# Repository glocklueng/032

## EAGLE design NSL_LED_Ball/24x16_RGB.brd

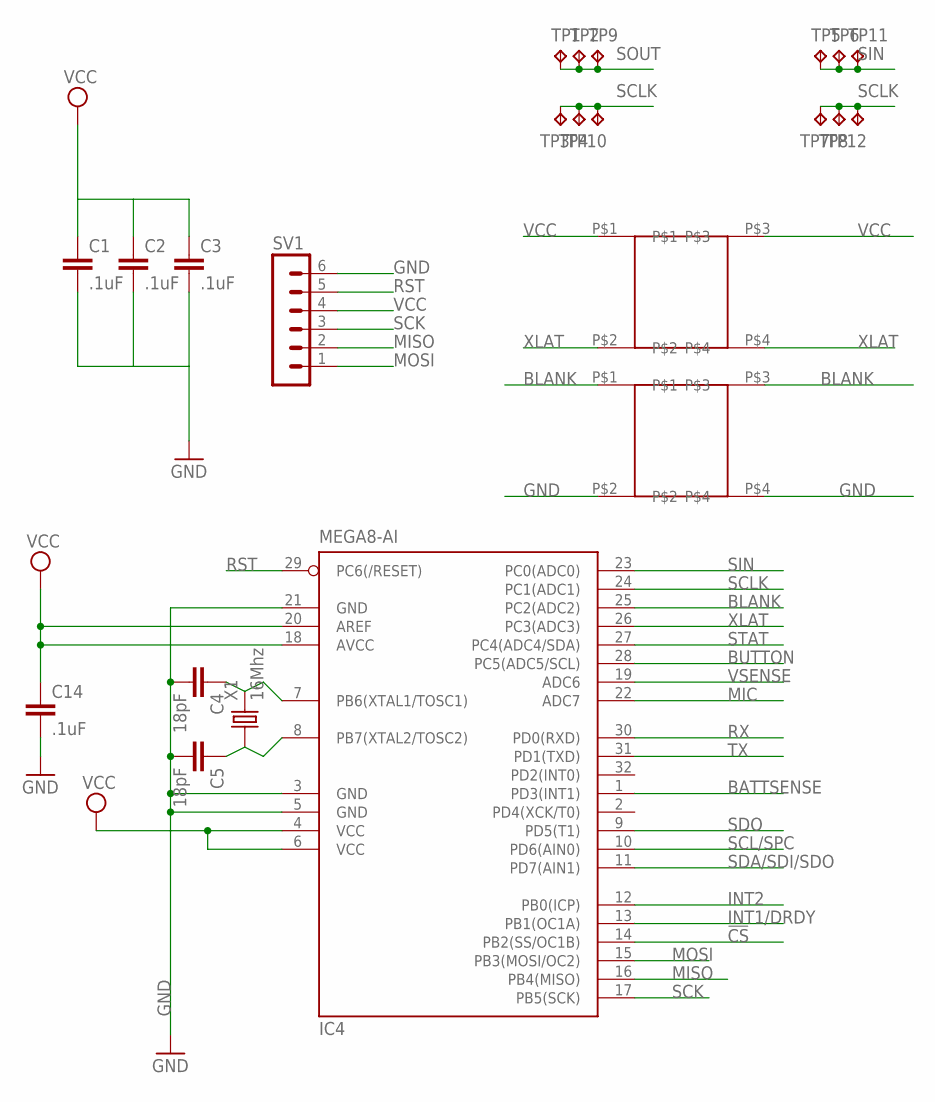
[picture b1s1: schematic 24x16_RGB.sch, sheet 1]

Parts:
C1, C2, C3, C14: .1uF; 0805
C4, C5: 18pF; 0805
IC4: MEGA8-AI; TQFP32-08
SLOT1, SLOT2: SLOT
SV1: MA06-1
TP1, TP2, TP3, TP4, TP5, TP6, TP7, TP8, TP9, TP10, TP11, TP12: TPTP20SQ; TP20SQ
X1: 16Mhz; 5032

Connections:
!CS: IC4.14 (PB2(SS/OC1B)); also elsewhere on the board
BATTSENSE: IC4.1 (PD3(INT1))
BLANK: IC4.25 (PC2(ADC2)), SLOT2.P$1, SLOT2.P$3; also elsewhere on the board
BUTTON: IC4.28 (PC5(ADC5/SCL)); also elsewhere on the board
GND: C1.2, C2.2, C3.2, C4.2, C5.2, C14.2, IC4.3 (GND), IC4.5 (GND), IC4.21 (GND), SLOT2.P$2, SLOT2.P$4, SV1.6; also elsewhere on the board
INT1/DRDY: IC4.13 (PB1(OC1A)); also elsewhere on the board
INT2: IC4.12 (PB0(ICP)); also elsewhere on the board
MIC: IC4.22 (ADC7); also elsewhere on the board
MISO: IC4.16 (PB4(MISO)), SV1.2
MOSI: IC4.15 (PB3(MOSI/OC2)), SV1.1
unnamed: C4.1, IC4.7 (PB6(XTAL1/TOSC1)), X1.2
unnamed: C5.1, IC4.8 (PB7(XTAL2/TOSC2)), X1.1
RST: IC4.29 (PC6(/RESET)), SV1.5; also elsewhere on the board
RX: IC4.30 (PD0(RXD)); also elsewhere on the board
SCK: IC4.17 (PB5(SCK)), SV1.3
SCL/SPC: IC4.10 (PD6(AIN0)); also elsewhere on the board
SCLK: IC4.24 (PC1(ADC1)), TP3.TP, TP4.TP, TP7.TP, TP8.TP, TP10.TP, TP12.TP; also elsewhere on the board
SDA/SDI/SDO: IC4.11 (PD7(AIN1)); also elsewhere on the board
SDO: IC4.9 (PD5(T1)); also elsewhere on the board
SIN: IC4.23 (PC0(ADC0)), TP5.TP, TP6.TP, TP11.TP; also elsewhere on the board
SOUT: TP1.TP, TP2.TP, TP9.TP; also elsewhere on the board
STAT: IC4.27 (PC4(ADC4/SDA)); also elsewhere on the board
TX: IC4.31 (PD1(TXD)); also elsewhere on the board
VCC: C1.1, C2.1, C3.1, C14.1, IC4.4 (VCC), IC4.6 (VCC), IC4.18 (AVCC), IC4.20 (AREF), SLOT1.P$1, SLOT1.P$3, SV1.4; also elsewhere on the board
VSENSE: IC4.19 (ADC6)
XLAT: IC4.26 (PC3(ADC3)), SLOT1.P$2, SLOT1.P$4; also elsewhere on the board

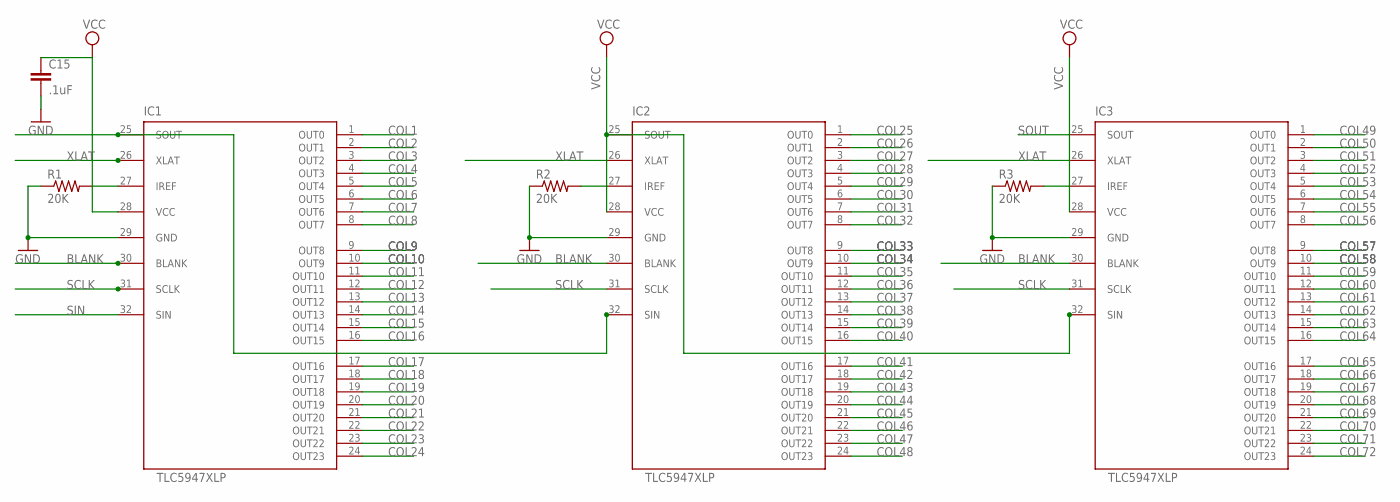
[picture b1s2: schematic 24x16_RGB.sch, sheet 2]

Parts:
C15: .1uF; 0805
IC1, IC2, IC3: TLC5947XLP; QFN32_XLP
R1, R2, R3: 20K; R0805

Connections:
BLANK: IC1.30 (BLANK), IC2.30 (BLANK), IC3.30 (BLANK); also elsewhere on the board
COL1: IC1.1 (OUT0); also elsewhere on the board
COL2: IC1.2 (OUT1); also elsewhere on the board
COL3: IC1.3 (OUT2); also elsewhere on the board
COL4: IC1.4 (OUT3); also elsewhere on the board
COL5: IC1.5 (OUT4); also elsewhere on the board
COL6: IC1.6 (OUT5); also elsewhere on the board
COL7: IC1.7 (OUT6); also elsewhere on the board
COL8: IC1.8 (OUT7); also elsewhere on the board
COL9: IC1.9 (OUT8); also elsewhere on the board
COL10: IC1.10 (OUT9); also elsewhere on the board
COL11: IC1.11 (OUT10); also elsewhere on the board
COL12: IC1.12 (OUT11); also elsewhere on the board
COL13: IC1.13 (OUT12); also elsewhere on the board
COL14: IC1.14 (OUT13); also elsewhere on the board
COL15: IC1.15 (OUT14); also elsewhere on the board
COL16: IC1.16 (OUT15); also elsewhere on the board
COL17: IC1.17 (OUT16); also elsewhere on the board
COL18: IC1.18 (OUT17); also elsewhere on the board
COL19: IC1.19 (OUT18); also elsewhere on the board
COL20: IC1.20 (OUT19); also elsewhere on the board
COL21: IC1.21 (OUT20); also elsewhere on the board
COL22: IC1.22 (OUT21); also elsewhere on the board
COL23: IC1.23 (OUT22); also elsewhere on the board
COL24: IC1.24 (OUT23); also elsewhere on the board
COL25: IC2.1 (OUT0); also elsewhere on the board
COL26: IC2.2 (OUT1); also elsewhere on the board
COL27: IC2.3 (OUT2); also elsewhere on the board
COL28: IC2.4 (OUT3); also elsewhere on the board
COL29: IC2.5 (OUT4); also elsewhere on the board
COL30: IC2.6 (OUT5); also elsewhere on the board
COL31: IC2.7 (OUT6); also elsewhere on the board
COL32: IC2.8 (OUT7); also elsewhere on the board
COL33: IC2.9 (OUT8); also elsewhere on the board
COL34: IC2.10 (OUT9); also elsewhere on the board
COL35: IC2.11 (OUT10); also elsewhere on the board
COL36: IC2.12 (OUT11); also elsewhere on the board
COL37: IC2.13 (OUT12); also elsewhere on the board
COL38: IC2.14 (OUT13); also elsewhere on the board
COL39: IC2.15 (OUT14); also elsewhere on the board
COL40: IC2.16 (OUT15); also elsewhere on the board
COL41: IC2.17 (OUT16); also elsewhere on the board
COL42: IC2.18 (OUT17); also elsewhere on the board
COL43: IC2.19 (OUT18); also elsewhere on the board
COL44: IC2.20 (OUT19); also elsewhere on the board
COL45: IC2.21 (OUT20); also elsewhere on the board
COL46: IC2.22 (OUT21); also elsewhere on the board
COL47: IC2.23 (OUT22); also elsewhere on the board
COL48: IC2.24 (OUT23); also elsewhere on the board
COL49: IC3.1 (OUT0); also elsewhere on the board
COL50: IC3.2 (OUT1); also elsewhere on the board
COL51: IC3.3 (OUT2); also elsewhere on the board
COL52: IC3.4 (OUT3); also elsewhere on the board
COL53: IC3.5 (OUT4); also elsewhere on the board
COL54: IC3.6 (OUT5); also elsewhere on the board
COL55: IC3.7 (OUT6); also elsewhere on the board
COL56: IC3.8 (OUT7); also elsewhere on the board
COL57: IC3.9 (OUT8); also elsewhere on the board
COL58: IC3.10 (OUT9); also elsewhere on the board
COL59: IC3.11 (OUT10); also elsewhere on the board
COL60: IC3.12 (OUT11); also elsewhere on the board
COL61: IC3.13 (OUT12); also elsewhere on the board
COL62: IC3.14 (OUT13); also elsewhere on the board
COL63: IC3.15 (OUT14); also elsewhere on the board
COL64: IC3.16 (OUT15); also elsewhere on the board
COL65: IC3.17 (OUT16); also elsewhere on the board
COL66: IC3.18 (OUT17); also elsewhere on the board
COL67: IC3.19 (OUT18); also elsewhere on the board
COL68: IC3.20 (OUT19); also elsewhere on the board
COL69: IC3.21 (OUT20); also elsewhere on the board
COL70: IC3.22 (OUT21); also elsewhere on the board
COL71: IC3.23 (OUT22); also elsewhere on the board
COL72: IC3.24 (OUT23); also elsewhere on the board
GND: C15.2, IC1.29 (GND), IC2.29 (GND), IC3.29 (GND), R1.1, R2.1, R3.1; also elsewhere on the board
HOLE: IC1.27 (IREF), R1.2
unnamed: IC2.27 (IREF), R2.2
unnamed: IC1.25 (SOUT), IC2.32 (SIN)
unnamed: IC3.27 (IREF), R3.2
unnamed: IC2.25 (SOUT), IC3.32 (SIN)
SCLK: IC1.31 (SCLK), IC2.31 (SCLK), IC3.31 (SCLK); also elsewhere on the board
SIN: IC1.32 (SIN); also elsewhere on the board
SOUT: IC3.25 (SOUT); also elsewhere on the board
VCC: C15.1, IC1.28 (VCC), IC2.28 (VCC), IC3.28 (VCC); also elsewhere on the board
XLAT: IC1.26 (XLAT), IC2.26 (XLAT), IC3.26 (XLAT); also elsewhere on the board

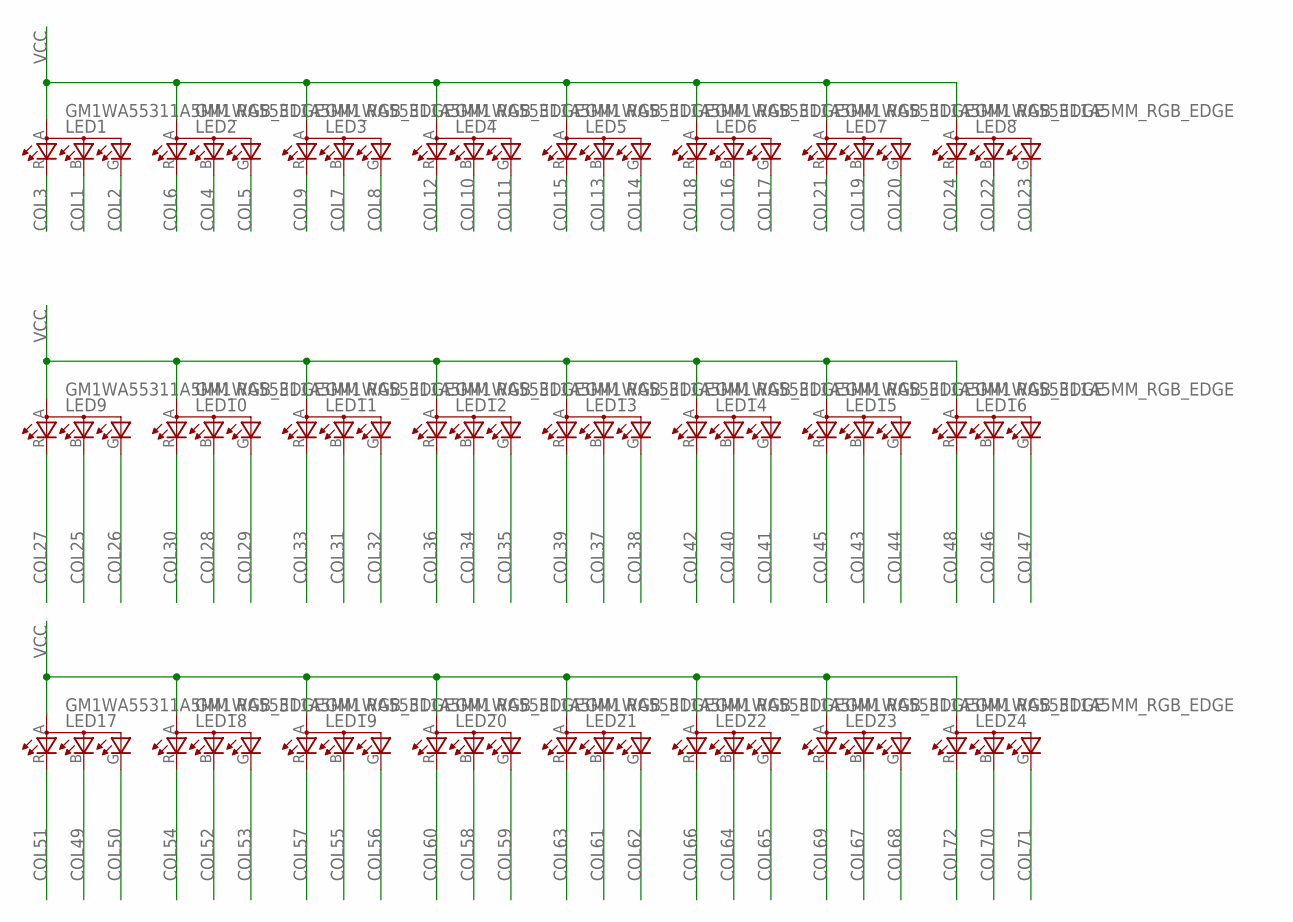
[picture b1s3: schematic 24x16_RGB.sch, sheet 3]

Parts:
LED1, LED2, LED3, LED4, LED5, LED6, LED7, LED8, LED9, LED10, LED11, LED12, LED13, LED14, LED15, LED16, LED17, LED18, LED19, LED20, LED21, LED22, LED23, LED24: GM1WA55311A5MM_RGB_EDGE; LED5MM_RGB_EDGE

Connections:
COL1: LED1.B (CBLUE); also elsewhere on the board
COL2: LED1.G (CGREEN); also elsewhere on the board
COL3: LED1.R (CRED); also elsewhere on the board
COL4: LED2.B (CBLUE); also elsewhere on the board
COL5: LED2.G (CGREEN); also elsewhere on the board
COL6: LED2.R (CRED); also elsewhere on the board
COL7: LED3.B (CBLUE); also elsewhere on the board
COL8: LED3.G (CGREEN); also elsewhere on the board
COL9: LED3.R (CRED); also elsewhere on the board
COL10: LED4.B (CBLUE); also elsewhere on the board
COL11: LED4.G (CGREEN); also elsewhere on the board
COL12: LED4.R (CRED); also elsewhere on the board
COL13: LED5.B (CBLUE); also elsewhere on the board
COL14: LED5.G (CGREEN); also elsewhere on the board
COL15: LED5.R (CRED); also elsewhere on the board
COL16: LED6.B (CBLUE); also elsewhere on the board
COL17: LED6.G (CGREEN); also elsewhere on the board
COL18: LED6.R (CRED); also elsewhere on the board
COL19: LED7.B (CBLUE); also elsewhere on the board
COL20: LED7.G (CGREEN); also elsewhere on the board
COL21: LED7.R (CRED); also elsewhere on the board
COL22: LED8.B (CBLUE); also elsewhere on the board
COL23: LED8.G (CGREEN); also elsewhere on the board
COL24: LED8.R (CRED); also elsewhere on the board
COL25: LED9.B (CBLUE); also elsewhere on the board
COL26: LED9.G (CGREEN); also elsewhere on the board
COL27: LED9.R (CRED); also elsewhere on the board
COL28: LED10.B (CBLUE); also elsewhere on the board
COL29: LED10.G (CGREEN); also elsewhere on the board
COL30: LED10.R (CRED); also elsewhere on the board
COL31: LED11.B (CBLUE); also elsewhere on the board
COL32: LED11.G (CGREEN); also elsewhere on the board
COL33: LED11.R (CRED); also elsewhere on the board
COL34: LED12.B (CBLUE); also elsewhere on the board
COL35: LED12.G (CGREEN); also elsewhere on the board
COL36: LED12.R (CRED); also elsewhere on the board
COL37: LED13.B (CBLUE); also elsewhere on the board
COL38: LED13.G (CGREEN); also elsewhere on the board
COL39: LED13.R (CRED); also elsewhere on the board
COL40: LED14.B (CBLUE); also elsewhere on the board
COL41: LED14.G (CGREEN); also elsewhere on the board
COL42: LED14.R (CRED); also elsewhere on the board
COL43: LED15.B (CBLUE); also elsewhere on the board
COL44: LED15.G (CGREEN); also elsewhere on the board
COL45: LED15.R (CRED); also elsewhere on the board
COL46: LED16.B (CBLUE); also elsewhere on the board
COL47: LED16.G (CGREEN); also elsewhere on the board
COL48: LED16.R (CRED); also elsewhere on the board
COL49: LED17.B (CBLUE); also elsewhere on the board
COL50: LED17.G (CGREEN); also elsewhere on the board
COL51: LED17.R (CRED); also elsewhere on the board
COL52: LED18.B (CBLUE); also elsewhere on the board
COL53: LED18.G (CGREEN); also elsewhere on the board
COL54: LED18.R (CRED); also elsewhere on the board
COL55: LED19.B (CBLUE); also elsewhere on the board
COL56: LED19.G (CGREEN); also elsewhere on the board
COL57: LED19.R (CRED); also elsewhere on the board
COL58: LED20.B (CBLUE); also elsewhere on the board
COL59: LED20.G (CGREEN); also elsewhere on the board
COL60: LED20.R (CRED); also elsewhere on the board
COL61: LED21.B (CBLUE); also elsewhere on the board
COL62: LED21.G (CGREEN); also elsewhere on the board
COL63: LED21.R (CRED); also elsewhere on the board
COL64: LED22.B (CBLUE); also elsewhere on the board
COL65: LED22.G (CGREEN); also elsewhere on the board
COL66: LED22.R (CRED); also elsewhere on the board
COL67: LED23.B (CBLUE); also elsewhere on the board
COL68: LED23.G (CGREEN); also elsewhere on the board
COL69: LED23.R (CRED); also elsewhere on the board
COL70: LED24.B (CBLUE); also elsewhere on the board
COL71: LED24.G (CGREEN); also elsewhere on the board
COL72: LED24.R (CRED); also elsewhere on the board
VCC: LED1.A, LED2.A, LED3.A, LED4.A, LED5.A, LED6.A, LED7.A, LED8.A, LED9.A, LED10.A, LED11.A, LED12.A, LED13.A, LED14.A, LED15.A, LED16.A, LED17.A, LED18.A, LED19.A, LED20.A, LED21.A, LED22.A, LED23.A, LED24.A; also elsewhere on the board

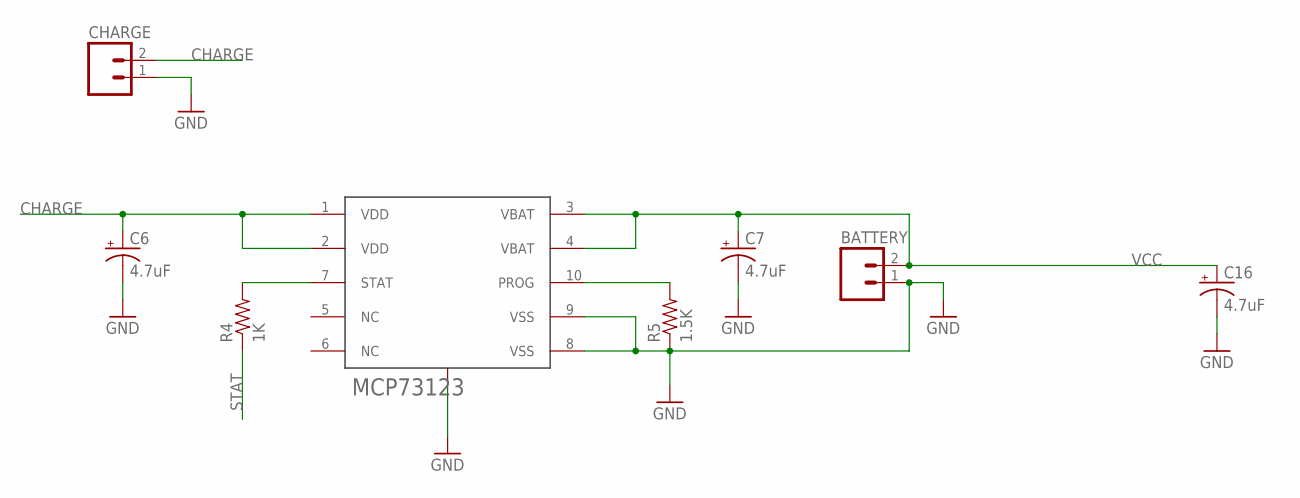
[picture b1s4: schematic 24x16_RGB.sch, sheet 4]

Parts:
BATTERY: M02PTH; 1X02
C6, C7, C16: 4.7uF; EIA3528
CHARGE: M02PTH; 1X02
IC5: MCP73123; DFN10_3X3
R4: 1K; 0805
R5: 1.5K; 0805

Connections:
CHARGE: C6.A (+), CHARGE.2, IC5.1 (VDD), IC5.2 (VDD)
GND: BATTERY.1, C6.C (-), C7.C (-), C16.C (-), CHARGE.1, IC5.8 (VSS), IC5.9 (VSS), IC5.EXP (GND), R5.1; also elsewhere on the board
unnamed: IC5.7 (STAT), R4.2
unnamed: IC5.10 (PROG), R5.2
STAT: R4.1; also elsewhere on the board
VCC: BATTERY.2, C7.A (+), C16.A (+), IC5.3 (VBAT), IC5.4 (VBAT); also elsewhere on the board

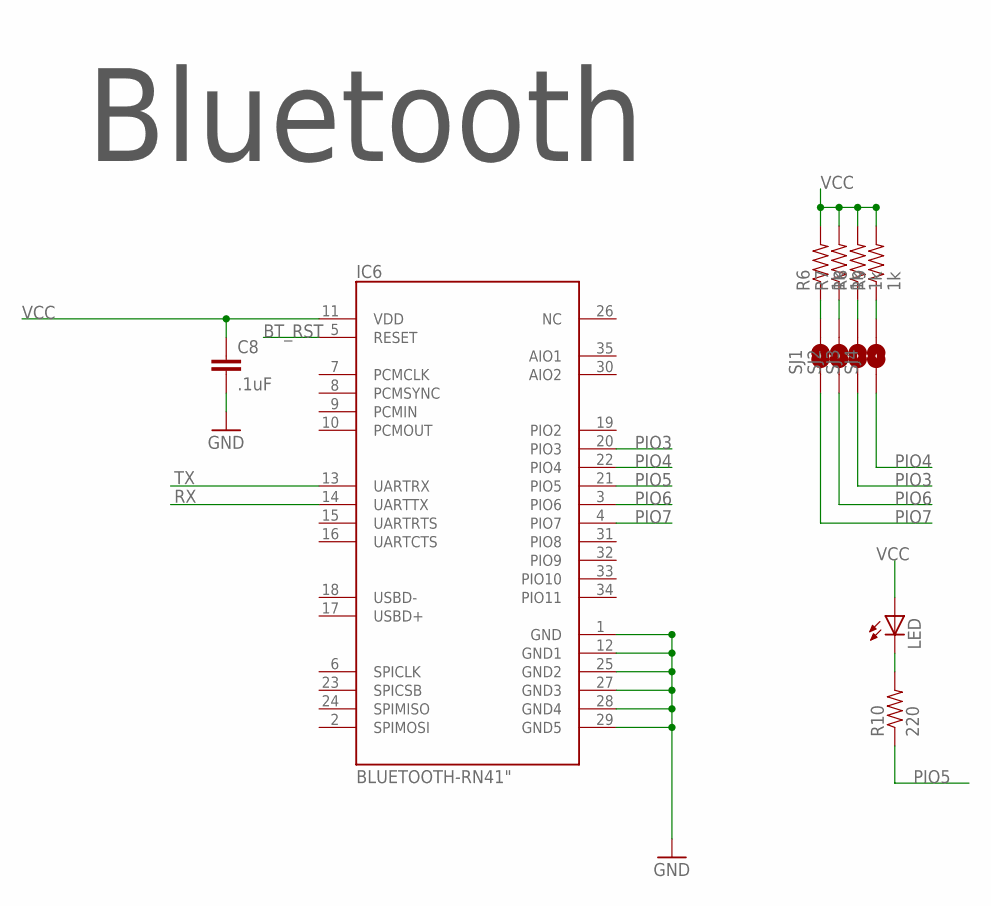
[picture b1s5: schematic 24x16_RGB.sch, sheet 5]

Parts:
C8: .1uF; 0805
IC6: BLUETOOTH-RN41"; RN41
LED: LEDCHIP-LED0603; CHIP-LED0603
R6, R7, R8, R9: 1k; 0805
R10: 220; 0805
SJ1, SJ2, SJ3, SJ4: SOLDERJUMPERNO; SJ_2S-NO

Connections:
BT_RST: IC6.5 (RESET); also elsewhere on the board
GND: C8.2, IC6.1 (GND), IC6.12 (GND1), IC6.25 (GND2), IC6.27 (GND3), IC6.28 (GND4), IC6.29 (GND5); also elsewhere on the board
unnamed: LED.C, R10.2
unnamed: R6.1, SJ1.2
unnamed: R8.1, SJ3.2
unnamed: R7.1, SJ2.2
unnamed: R9.1, SJ4.2
PIO3: IC6.20 (PIO3), SJ3.1
PIO4: IC6.22 (PIO4), SJ4.1
PIO5: IC6.21 (PIO5), R10.1
PIO6: IC6.3 (PIO6), SJ2.1
PIO7: IC6.4 (PIO7), SJ1.1
RX: IC6.14 (UARTTX); also elsewhere on the board
TX: IC6.13 (UARTRX); also elsewhere on the board
VCC: C8.1, IC6.11 (VDD), LED.A, R6.2, R7.2, R8.2, R9.2; also elsewhere on the board

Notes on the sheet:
Bluetooth

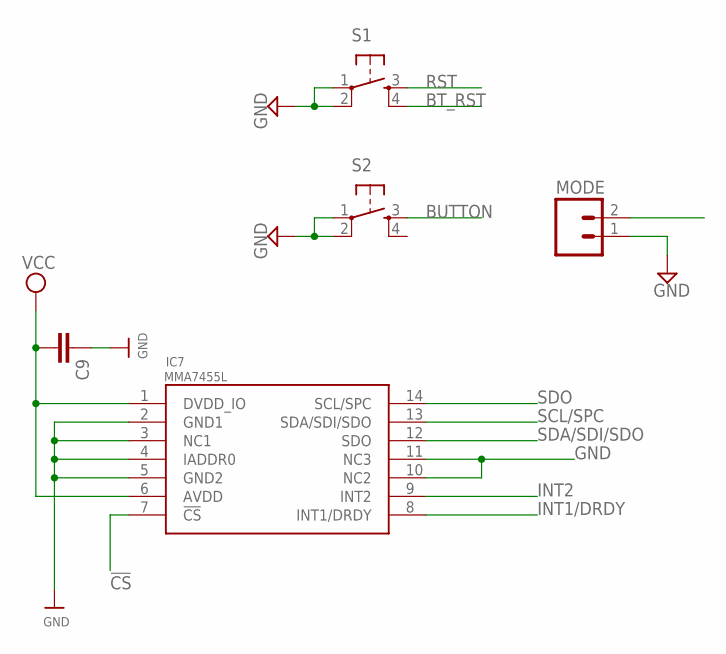
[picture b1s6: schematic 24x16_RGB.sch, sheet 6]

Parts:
C9: CAP0805; 0805
IC7: MMA7455L; LGA-14
MODE: M02PTH; 1X02
S1, S2: TAC_SWITCHSMD; TACTILE_SWITCH_SMD

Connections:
!CS: IC7.7 (!CS); also elsewhere on the board
BT_RST: S1.4; also elsewhere on the board
BUTTON: MODE.2, S2.3; also elsewhere on the board
GND: C9.1, IC7.2 (GND1), IC7.3 (NC1), IC7.4 (IADDR0), IC7.5 (GND2), IC7.10 (NC2), IC7.11 (NC3), MODE.1, S1.1, S1.2, S2.1, S2.2; also elsewhere on the board
INT1/DRDY: IC7.8 (INT1/DRDY); also elsewhere on the board
INT2: IC7.9 (INT2); also elsewhere on the board
RST: S1.3; also elsewhere on the board
SCL/SPC: IC7.13 (SDA/SDI/SDO); also elsewhere on the board
SDA/SDI/SDO: IC7.12 (SDO); also elsewhere on the board
SDO: IC7.14 (SCL/SPC); also elsewhere on the board
VCC: C9.2, IC7.1 (DVDD_IO), IC7.6 (AVDD); also elsewhere on the board

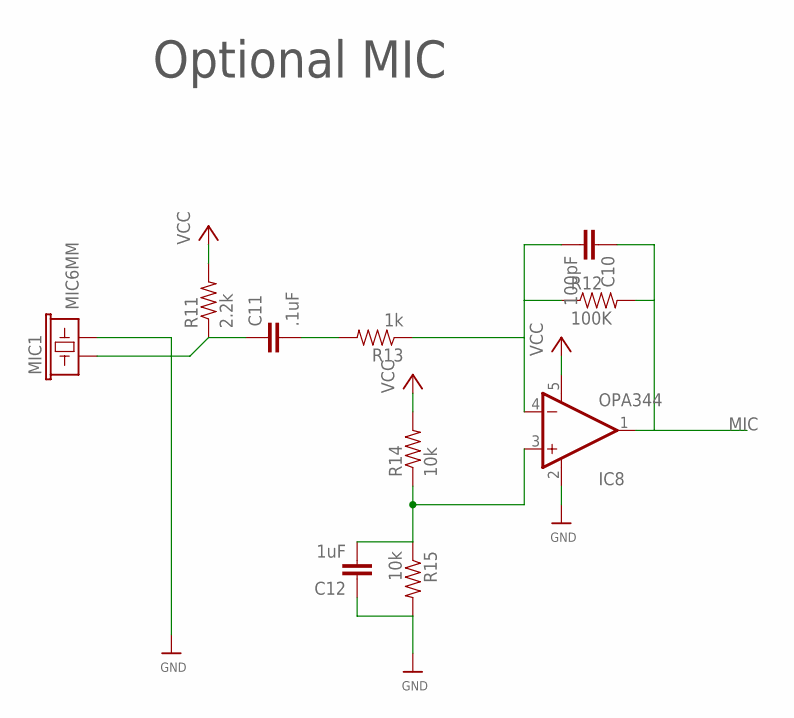
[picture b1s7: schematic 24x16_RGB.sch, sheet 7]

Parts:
C10: 100pF; 0805
C11: .1uF; 0805
C12: 1uF; 0805
IC8: OPA344; SOT23-5
MIC1: MIC6MM; MIC-6MM
R11: 2.2k; 0805
R12: 100K; 0805
R13: 1k; 0805
R14, R15: 10k; 0805

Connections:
GND: C12.1, IC8.2 (V-), MIC1.2, R15.2; also elsewhere on the board
MIC: C10.1, IC8.1 (OUT), R12.2; also elsewhere on the board
unnamed: C11.2, R13.2
unnamed: C11.1, MIC1.1, R11.1
unnamed: C12.2, IC8.3 (+IN), R14.1, R15.1
unnamed: C10.2, IC8.4 (-IN), R12.1, R13.1
VCC: IC8.5 (V+), R11.2, R14.2; also elsewhere on the board

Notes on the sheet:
Optional MIC

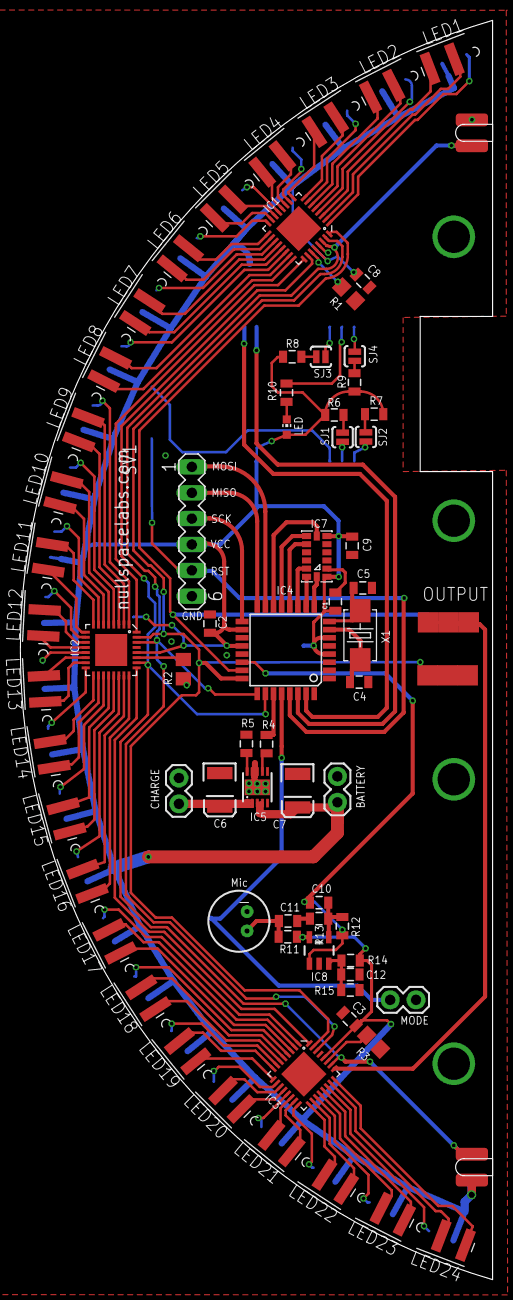
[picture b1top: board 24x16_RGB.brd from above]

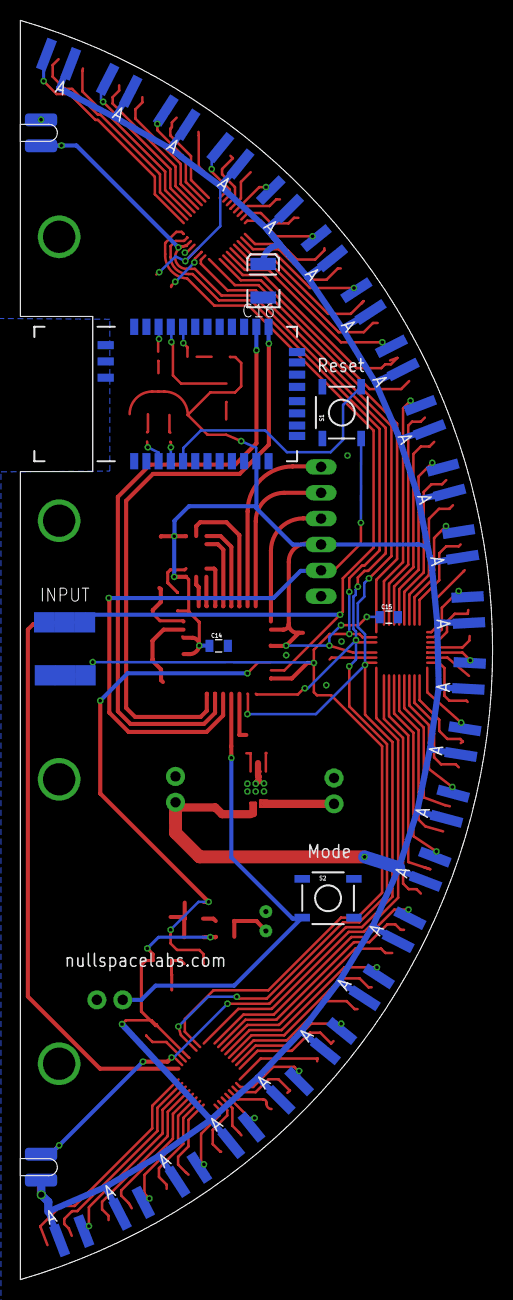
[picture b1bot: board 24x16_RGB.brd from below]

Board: 2 copper layers, 46.4 x 123.7 mm, 89 parts (12 on the bottom side), 119 nets.

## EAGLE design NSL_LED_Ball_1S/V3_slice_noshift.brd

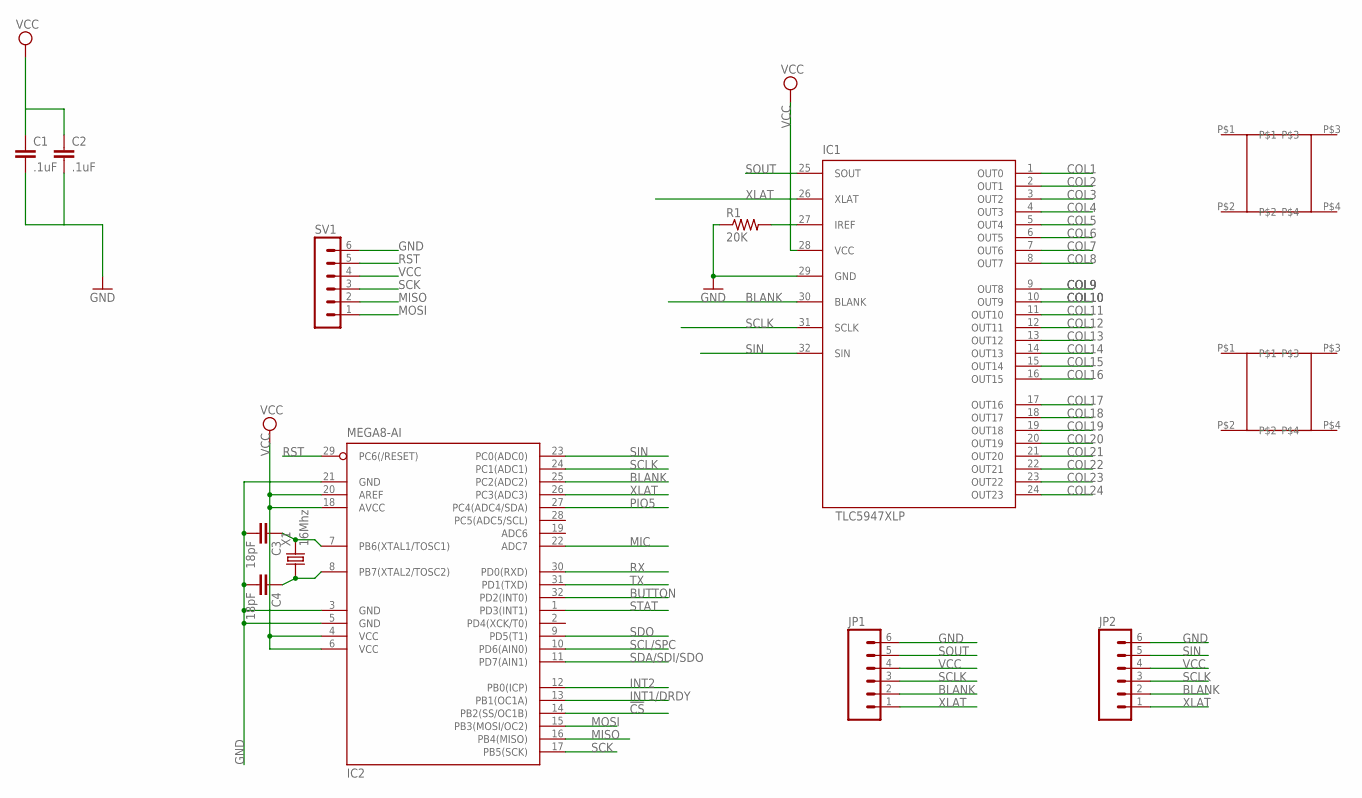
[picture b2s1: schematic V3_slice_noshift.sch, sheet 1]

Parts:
C1, C2: .1uF; 0805
C3, C4: 18pF; 0805
IC1: TLC5947XLP; QFN32_XLP
IC2: MEGA8-AI; TQFP32-08
JP1, JP2: M061X06-SMD_EDGE_FEMALE; 1X06-SMD_EDGE
R1: 20K; R0805
SLOT1, SLOT2: SLOT
SV1: MA06-1
X1: 16Mhz; 5032

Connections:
!CS: IC2.14 (PB2(SS/OC1B)); also elsewhere on the board
BLANK: IC1.30 (BLANK), IC2.25 (PC2(ADC2)), JP1.2, JP2.2
BUTTON: IC2.32 (PD2(INT0)); also elsewhere on the board
COL1: IC1.1 (OUT0); also elsewhere on the board
COL2: IC1.2 (OUT1); also elsewhere on the board
COL3: IC1.3 (OUT2); also elsewhere on the board
COL4: IC1.4 (OUT3); also elsewhere on the board
COL5: IC1.5 (OUT4); also elsewhere on the board
COL6: IC1.6 (OUT5); also elsewhere on the board
COL7: IC1.7 (OUT6); also elsewhere on the board
COL8: IC1.8 (OUT7); also elsewhere on the board
COL9: IC1.9 (OUT8); also elsewhere on the board
COL10: IC1.10 (OUT9); also elsewhere on the board
COL11: IC1.11 (OUT10); also elsewhere on the board
COL12: IC1.12 (OUT11); also elsewhere on the board
COL13: IC1.13 (OUT12); also elsewhere on the board
COL14: IC1.14 (OUT13); also elsewhere on the board
COL15: IC1.15 (OUT14); also elsewhere on the board
COL16: IC1.16 (OUT15); also elsewhere on the board
COL17: IC1.17 (OUT16); also elsewhere on the board
COL18: IC1.18 (OUT17); also elsewhere on the board
COL19: IC1.19 (OUT18); also elsewhere on the board
COL20: IC1.20 (OUT19); also elsewhere on the board
COL21: IC1.21 (OUT20); also elsewhere on the board
COL22: IC1.22 (OUT21); also elsewhere on the board
COL23: IC1.23 (OUT22); also elsewhere on the board
COL24: IC1.24 (OUT23); also elsewhere on the board
GND: C1.2, C2.2, C3.2, C4.2, IC1.29 (GND), IC2.3 (GND), IC2.5 (GND), IC2.21 (GND), JP1.6, JP2.6, R1.1, SV1.6; also elsewhere on the board
INT1/DRDY: IC2.13 (PB1(OC1A)); also elsewhere on the board
INT2: IC2.12 (PB0(ICP)); also elsewhere on the board
MIC: IC2.22 (ADC7); also elsewhere on the board
MISO: IC2.16 (PB4(MISO)), SV1.2
MOSI: IC2.15 (PB3(MOSI/OC2)), SV1.1
unnamed: C3.1, IC2.7 (PB6(XTAL1/TOSC1)), X1.2
unnamed: C4.1, IC2.8 (PB7(XTAL2/TOSC2)), X1.1
unnamed: IC1.27 (IREF), R1.2
PIO5: IC2.27 (PC4(ADC4/SDA)); also elsewhere on the board
RST: IC2.29 (PC6(/RESET)), SV1.5; also elsewhere on the board
RX: IC2.30 (PD0(RXD)); also elsewhere on the board
SCK: IC2.17 (PB5(SCK)), SV1.3
SCL/SPC: IC2.10 (PD6(AIN0)); also elsewhere on the board
SCLK: IC1.31 (SCLK), IC2.24 (PC1(ADC1)), JP1.3, JP2.3
SDA/SDI/SDO: IC2.11 (PD7(AIN1)); also elsewhere on the board
SDO: IC2.9 (PD5(T1)); also elsewhere on the board
SIN: IC1.32 (SIN), IC2.23 (PC0(ADC0)), JP2.5
SOUT: IC1.25 (SOUT), JP1.5
STAT: IC2.1 (PD3(INT1)); also elsewhere on the board
TX: IC2.31 (PD1(TXD)); also elsewhere on the board
VCC: C1.1, C2.1, IC1.28 (VCC), IC2.4 (VCC), IC2.6 (VCC), IC2.18 (AVCC), IC2.20 (AREF), JP1.4, JP2.4, SV1.4; also elsewhere on the board
XLAT: IC1.26 (XLAT), IC2.26 (PC3(ADC3)), JP1.1, JP2.1

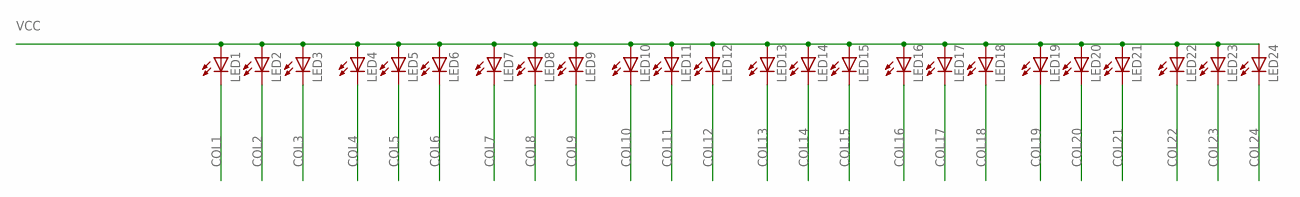
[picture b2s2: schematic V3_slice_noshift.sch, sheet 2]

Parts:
LED1, LED2, LED3, LED4, LED5, LED6, LED7, LED8, LED9, LED10, LED11, LED12, LED13, LED14, LED15, LED16, LED17, LED18, LED19, LED20, LED21, LED22, LED23, LED24: LEDIRL80A; IRL80A

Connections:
COL1: LED1.K (C); also elsewhere on the board
COL2: LED2.K (C); also elsewhere on the board
COL3: LED3.K (C); also elsewhere on the board
COL4: LED4.K (C); also elsewhere on the board
COL5: LED5.K (C); also elsewhere on the board
COL6: LED6.K (C); also elsewhere on the board
COL7: LED7.K (C); also elsewhere on the board
COL8: LED8.K (C); also elsewhere on the board
COL9: LED9.K (C); also elsewhere on the board
COL10: LED10.K (C); also elsewhere on the board
COL11: LED11.K (C); also elsewhere on the board
COL12: LED12.K (C); also elsewhere on the board
COL13: LED13.K (C); also elsewhere on the board
COL14: LED14.K (C); also elsewhere on the board
COL15: LED15.K (C); also elsewhere on the board
COL16: LED16.K (C); also elsewhere on the board
COL17: LED17.K (C); also elsewhere on the board
COL18: LED18.K (C); also elsewhere on the board
COL19: LED19.K (C); also elsewhere on the board
COL20: LED20.K (C); also elsewhere on the board
COL21: LED21.K (C); also elsewhere on the board
COL22: LED22.K (C); also elsewhere on the board
COL23: LED23.K (C); also elsewhere on the board
COL24: LED24.K (C); also elsewhere on the board
VCC: LED1.A, LED2.A, LED3.A, LED4.A, LED5.A, LED6.A, LED7.A, LED8.A, LED9.A, LED10.A, LED11.A, LED12.A, LED13.A, LED14.A, LED15.A, LED16.A, LED17.A, LED18.A, LED19.A, LED20.A, LED21.A, LED22.A, LED23.A, LED24.A; also elsewhere on the board

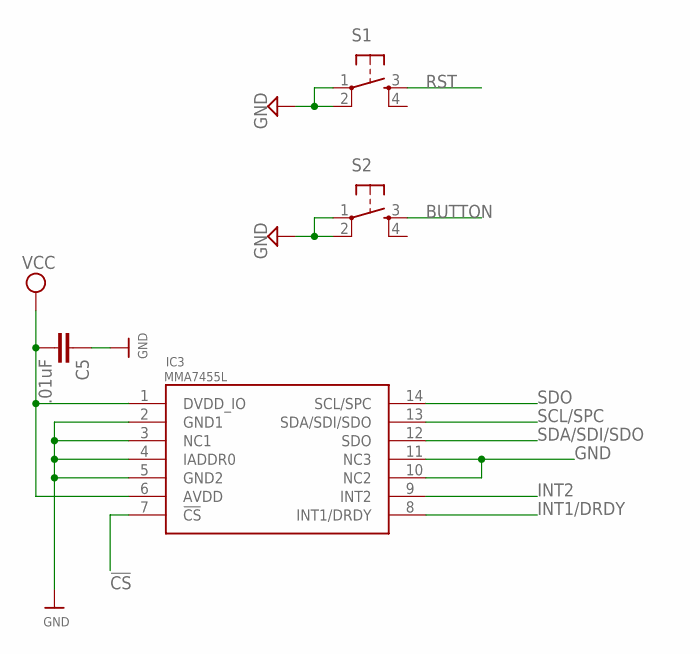
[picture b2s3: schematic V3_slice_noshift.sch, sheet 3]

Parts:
C5: .01uF; 0805
IC3: MMA7455L; LGA-14
S1, S2: TAC_SWITCHSMD; TACTILE_SWITCH_SMD

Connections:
!CS: IC3.7 (!CS); also elsewhere on the board
BUTTON: S2.3; also elsewhere on the board
GND: C5.1, IC3.2 (GND1), IC3.3 (NC1), IC3.4 (IADDR0), IC3.5 (GND2), IC3.10 (NC2), IC3.11 (NC3), S1.1, S1.2, S2.1, S2.2; also elsewhere on the board
INT1/DRDY: IC3.8 (INT1/DRDY); also elsewhere on the board
INT2: IC3.9 (INT2); also elsewhere on the board
RST: S1.3; also elsewhere on the board
SCL/SPC: IC3.13 (SDA/SDI/SDO); also elsewhere on the board
SDA/SDI/SDO: IC3.12 (SDO); also elsewhere on the board
SDO: IC3.14 (SCL/SPC); also elsewhere on the board
VCC: C5.2, IC3.1 (DVDD_IO), IC3.6 (AVDD); also elsewhere on the board

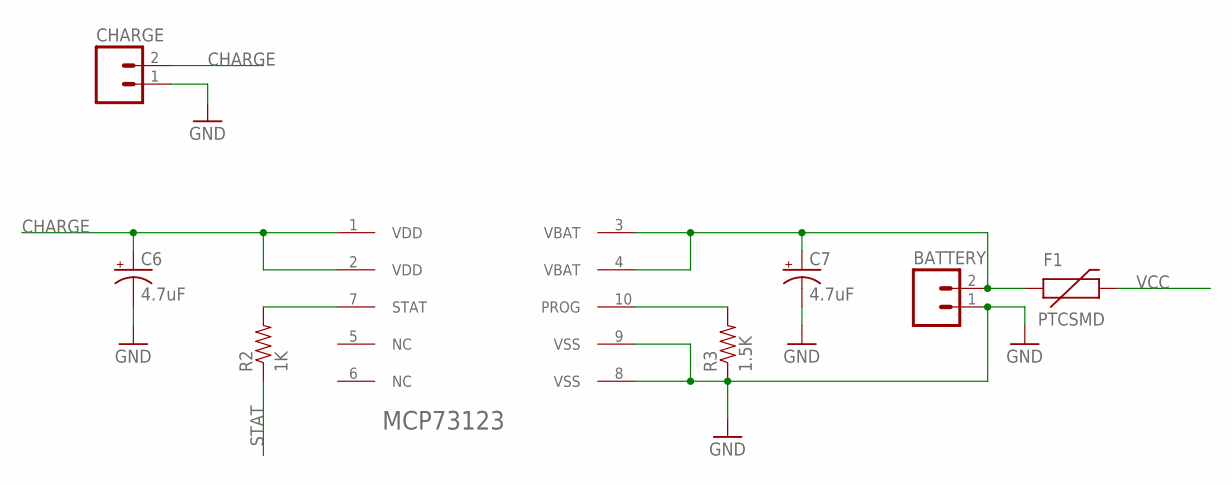
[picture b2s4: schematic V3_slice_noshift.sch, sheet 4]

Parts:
BATTERY: M02PTH; 1X02
C6, C7: 4.7uF; EIA3528
CHARGE: M02-JST-2-PTH-NO_SILK; JST-2-PTH-NS
F1: PTCSMD; PTC-1206
IC4: MCP73123; DFN10_3X3
R2: 1K; 0805
R3: 1.5K; 0805

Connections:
CHARGE: C6.A (+), CHARGE.2, IC4.1 (VDD), IC4.2 (VDD)
GND: BATTERY.1, C6.C (-), C7.C (-), CHARGE.1, IC4.8 (VSS), IC4.9 (VSS), R3.1; also elsewhere on the board
unnamed: IC4.7 (STAT), R2.2
unnamed: IC4.10 (PROG), R3.2
STAT: R2.1; also elsewhere on the board
VBAT: BATTERY.2, C7.A (+), F1.1, IC4.3 (VBAT), IC4.4 (VBAT)
VCC: F1.2; also elsewhere on the board

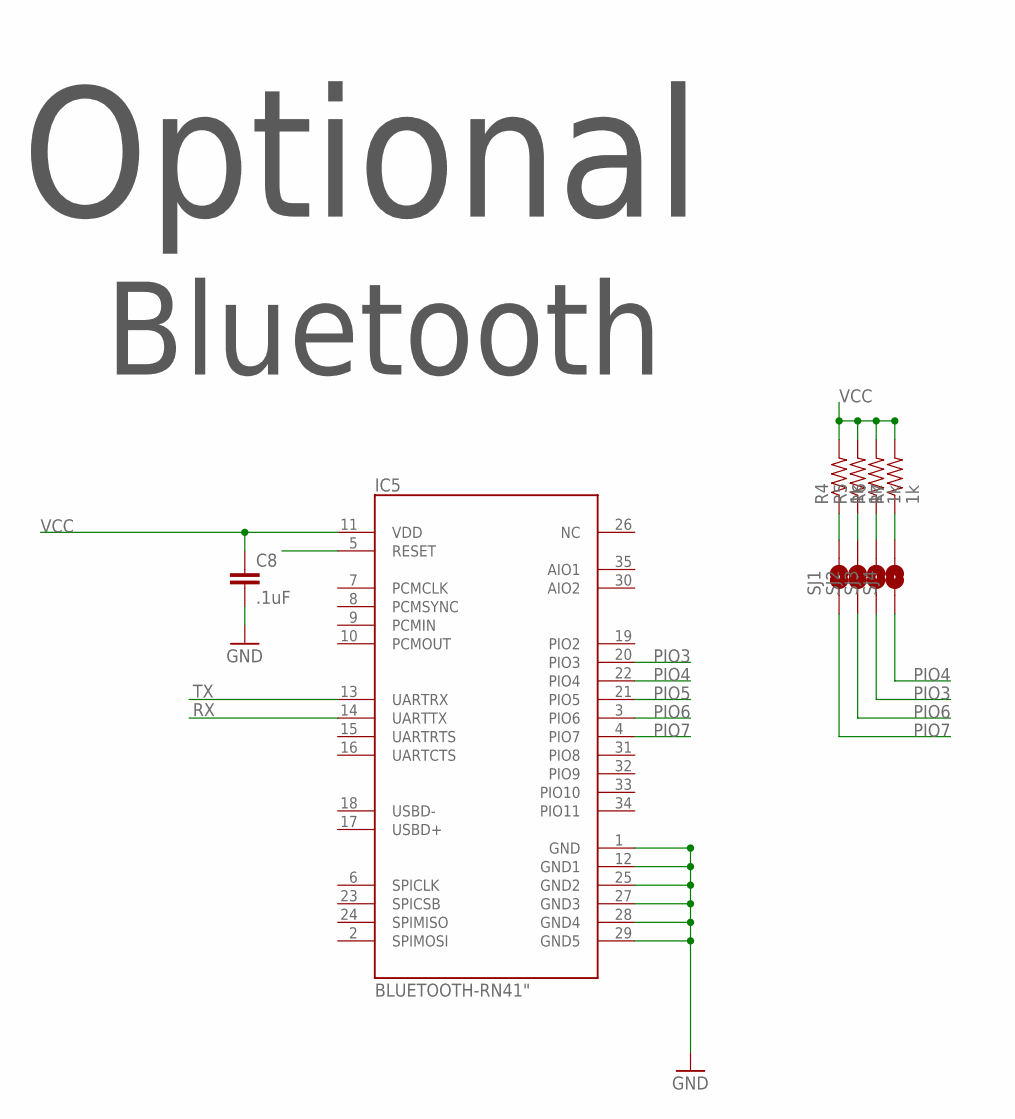
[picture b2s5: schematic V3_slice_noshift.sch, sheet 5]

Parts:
C8: .1uF; 0805
IC5: BLUETOOTH-RN41"; RN41
R4, R5, R6, R7: 1k; 0805
SJ1, SJ2, SJ3, SJ4: SOLDERJUMPERNO; SJ_2S-NO

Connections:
GND: C8.2, IC5.1 (GND), IC5.12 (GND1), IC5.25 (GND2), IC5.27 (GND3), IC5.28 (GND4), IC5.29 (GND5); also elsewhere on the board
unnamed: R4.1, SJ1.2
unnamed: R6.1, SJ3.2
unnamed: R5.1, SJ2.2
unnamed: R7.1, SJ4.2
PIO3: IC5.20 (PIO3), SJ3.1
PIO4: IC5.22 (PIO4), SJ4.1
PIO5: IC5.21 (PIO5); also elsewhere on the board
PIO6: IC5.3 (PIO6), SJ2.1
PIO7: IC5.4 (PIO7), SJ1.1
RST: IC5.5 (RESET); also elsewhere on the board
RX: IC5.14 (UARTTX); also elsewhere on the board
TX: IC5.13 (UARTRX); also elsewhere on the board
VCC: C8.1, IC5.11 (VDD), R4.2, R5.2, R6.2, R7.2; also elsewhere on the board

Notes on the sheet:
Bluetooth
Optional
